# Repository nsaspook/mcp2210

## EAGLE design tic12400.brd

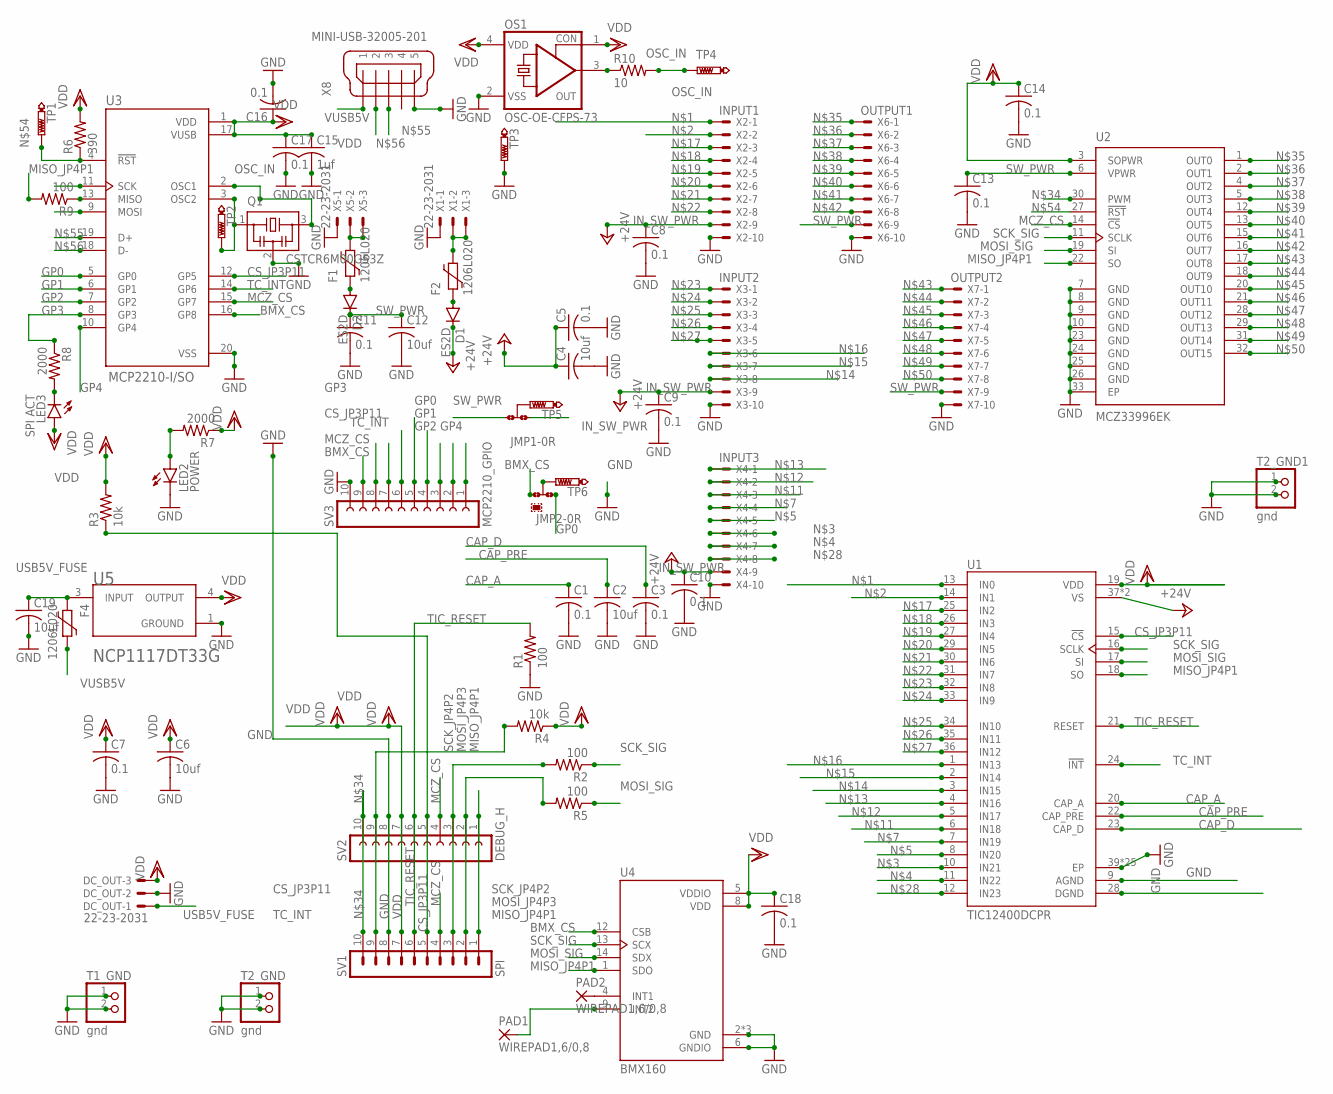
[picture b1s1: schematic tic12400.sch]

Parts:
C1, C3, C5, C7, C8, C9, C10, C11, C13, C14, C16, C17, C18: 0.1; C0805
C2, C4, C6, C12, C19: 10uf; C0805
C15: 1uf; C0805
D1, D2: ES2D; SMB
DC_OUT: 22-23-2031
F1, F2, F4: 1206L020; 1206L
JMP1: +24_CONNECT; A0R-JMP
JMP2: CS8_CS0; A0R-JMP
LED2: POWER; CHIP-LED0805
LED3: SPI ACT; CHIP-LED0805
OS1: OSC-OE-CFPS-73; 7.2X5.2-4-PAD
PAD1, PAD2: WIREPAD1,6/0,8; 1,6/0,8
Q1: CSTCR6M00G53Z; CSTCR6M
R1, R2, R5, R9: 100; R0805
R3, R4: 10k; R0805
R6: 390; R0805
R7, R8: 2000; R0805
R10: 10; R0805
SV1: SPI; MA10-1
SV2: DEBUG_H; FE10
SV3: MCP2210_GPIO; FE10
T1_GND, T2_GND, T2_GND1: gnd; 1X02
TP1, TP2, TP3, TP4, TP5, TP6: PTR1B1,27; B1,27
U1: TIC12400DCPR; SOP50P640X120-38N
U2: MCZ33996EK; SOP65P1030X265-33N
U3: MCP2210-I/SO; SOP65P780X200-20N
U4: BMX160; PQFN50P250X300X100-14N
U5: ON_SEMICONDUCTOR_NCP1117DT33GON_SEMICONDUCTOR_NCP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; ON_SEMICONDUCTOR_NCP1117DT33G_0
X1, X5: 22-23-2031
X2: INPUT1; KK-156-10
X3: INPUT2; KK-156-10
X4: INPUT3; KK-156-10
X6: OUTPUT1; KK-156-10
X7: OUTPUT2; KK-156-10
X8: MINI-USB-32005-201; 32005-201

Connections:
BMX_CS: JMP2.1, SV3.9, U3.16 (GP8), U4.12 (CSB)
CAP_A: C1.1, U1.20 (CAP_A)
CAP_D: C3.1, U1.23 (CAP_D)
CAP_PRE: C2.1, U1.22 (CAP_PRE)
CS_JP3P11: R3.1, SV1.5, SV2.5, SV3.6, U1.15 (!CS), U3.12 (GP5)
GND: C1.2, C2.2, C3.2, C4.2, C5.2, C6.2, C7.2, C8.2, C9.2, C10.2, C11.2, C12.2, C13.2, C14.2, C15.2, C16.2, C17.2, C18.2, C19.2, DC_OUT.2, LED2.C, OS1.2 (VSS), Q1.2, R1.1, SV1.8, SV2.8, SV3.10, T1_GND.1, T1_GND.2, T2_GND.1, T2_GND.2, T2_GND1.1, T2_GND1.2, TP3.TP, U1.9 (AGND), U1.28 (DGND), U1.39 (EP), U1.40 (EP), U1.41 (EP), U1.42 (EP), U1.43 (EP), U1.44 (EP), U1.45 (EP), U1.46 (EP), U1.47 (EP), U1.48 (EP), U1.49 (EP), U1.50 (EP), U1.51 (EP), U1.52 (EP), U1.53 (EP), U1.54 (EP), U1.55 (EP), U1.56 (EP), U1.57 (EP), U1.58 (EP), U1.59 (EP), U1.60 (EP), U1.61 (EP), U1.62 (EP), U1.63 (EP), U2.7 (GND), U2.8 (GND), U2.9 (GND), U2.10 (GND), U2.23 (GND), U2.24 (GND), U2.25 (GND), U2.26 (GND), U2.33 (EP), U3.20 (VSS), U4.2 (GND), U4.3 (GND), U4.6 (GNDIO), U4.7 (GND), U5.1 (GROUND), X1.1, X2.10, X3.10, X4.10, X5.1, X6.10, X7.10, X8.5
GP0: JMP2.3, SV3.1, U3.5 (GP0)
GP1: SV3.2, U3.6 (GP1)
GP2: SV3.3, U3.7 (GP2)
GP3: R8.1, SV3.4, U3.8 (GP3)
GP4: SV3.5, U3.10 (GP4)
IN_SW_PWR: C4.1, C5.1, C8.1, C9.1, C10.1, D1.C, JMP1.3, U1.37 (VS), U1.38 (VS), X2.9, X3.9, X4.9
MCZ_CS: SV1.4, SV2.4, SV3.8, U2.14 (!CS), U3.15 (GP7)
MISO_JP4P1: R9.2, SV1.1, SV2.1, U1.18 (SO), U2.22 (SO), U4.1 (SDO)
MOSI_JP4P3: R5.2, SV1.2, SV2.2
MOSI_SIG: R5.1, U1.17 (SI), U2.19 (SI), U3.9 (MOSI), U4.14 (SDX)
unnamed: U1.13 (IN0), X2.1
unnamed: U1.14 (IN1), X2.2
unnamed: U1.10 (IN21), X4.6
unnamed: U1.11 (IN22), X4.7
unnamed: U1.8 (IN20), X4.5
unnamed: JMP2.2, TP6.TP
unnamed: U1.7 (IN19), X4.4
unnamed: U1.6 (IN18), X4.3
unnamed: U1.5 (IN17), X4.2
unnamed: U1.4 (IN16), X4.1
unnamed: U1.3 (IN15), X3.8
unnamed: U1.2 (IN14), X3.7
unnamed: U1.1 (IN13), X3.6
unnamed: U1.25 (IN2), X2.3
unnamed: U1.26 (IN3), X2.4
unnamed: U1.27 (IN4), X2.5
unnamed: U1.29 (IN5), X2.6
unnamed: U1.30 (IN6), X2.7
unnamed: U1.31 (IN7), X2.8
unnamed: U1.32 (IN8), X3.1
unnamed: U1.33 (IN9), X3.2
unnamed: U1.34 (IN10), X3.3
unnamed: U1.35 (IN11), X3.4
unnamed: U1.36 (IN12), X3.5
unnamed: U1.12 (IN23), X4.8
unnamed: F2.1, X1.2, X1.3
unnamed: D2.A, F1.2
unnamed: F1.1, X5.2, X5.3
unnamed: SV1.10, SV2.10, U2.30 (PWM)
unnamed: U2.1 (OUT0), X6.1
unnamed: U2.2 (OUT1), X6.2
unnamed: U2.4 (OUT2), X6.3
unnamed: U2.5 (OUT3), X6.4
unnamed: U2.12 (OUT4), X6.5
unnamed: U2.13 (OUT5), X6.6
unnamed: U2.15 (OUT6), X6.7
unnamed: U2.16 (OUT7), X6.8
unnamed: U2.17 (OUT8), X7.1
unnamed: U2.18 (OUT9), X7.2
unnamed: U2.20 (OUT10), X7.3
unnamed: U2.21 (OUT11), X7.4
unnamed: U2.28 (OUT12), X7.5
unnamed: U2.29 (OUT13), X7.6
unnamed: U2.31 (OUT14), X7.7
unnamed: U2.32 (OUT15), X7.8
unnamed: D1.A, F2.2
unnamed: Q1.1, TP2.TP, U3.3 (OSC2)
unnamed: R6.1, TP1.TP, U2.27 (!RST), U3.4 (!RST)
unnamed 64: U3.19 (D+), X8.3; also elsewhere on the board
unnamed 65: U3.18 (D-), X8.2; also elsewhere on the board
unnamed: LED2.A, R7.2
unnamed: LED3.C, R8.2
unnamed: R9.1, U3.13 (MISO)
unnamed: OS1.3 (OUT), R10.1
unnamed: JMP1.2, TP5.TP
unnamed 71: PAD2.1, U4.4 (INT1); also elsewhere on the board
unnamed 72: PAD1.1, U4.9 (INT2); also elsewhere on the board
OSC_IN: Q1.3, R10.2, TP4.TP, U3.2 (OSC1)
SCK_JP4P2: R2.2, SV1.3, SV2.3
SCK_SIG: R2.1, U1.16 (SCLK), U2.11 (SCLK), U3.11 (SCK), U4.13 (SCX)
SW_PWR: C11.1, C12.1, C13.1, D2.C, JMP1.1, U2.6 (VPWR), X6.9, X7.9
TC_INT: R4.2, SV1.9, SV2.9, SV3.7, U1.24 (!INT), U3.14 (GP6)
TIC_RESET: R1.2, SV1.6, SV2.6, U1.21 (RESET)
USB5V_FUSE: C19.1, DC_OUT.1, F4.2, U5.3 (INPUT)
VDD: C6.1, C7.1, C14.1, C15.1, C16.1, C17.1, C18.1, DC_OUT.3, LED3.A, OS1.1 (CON), OS1.4 (VDD), R3.2, R4.1, R6.2, R7.1, SV1.7, SV2.7, U1.19 (VDD), U2.3 (SOPWR), U3.1 (VDD), U3.17 (VUSB), U4.5 (VDDIO), U4.8 (VDD), U5.4 (OUTPUT)
VUSB5V: F4.1, X8.1

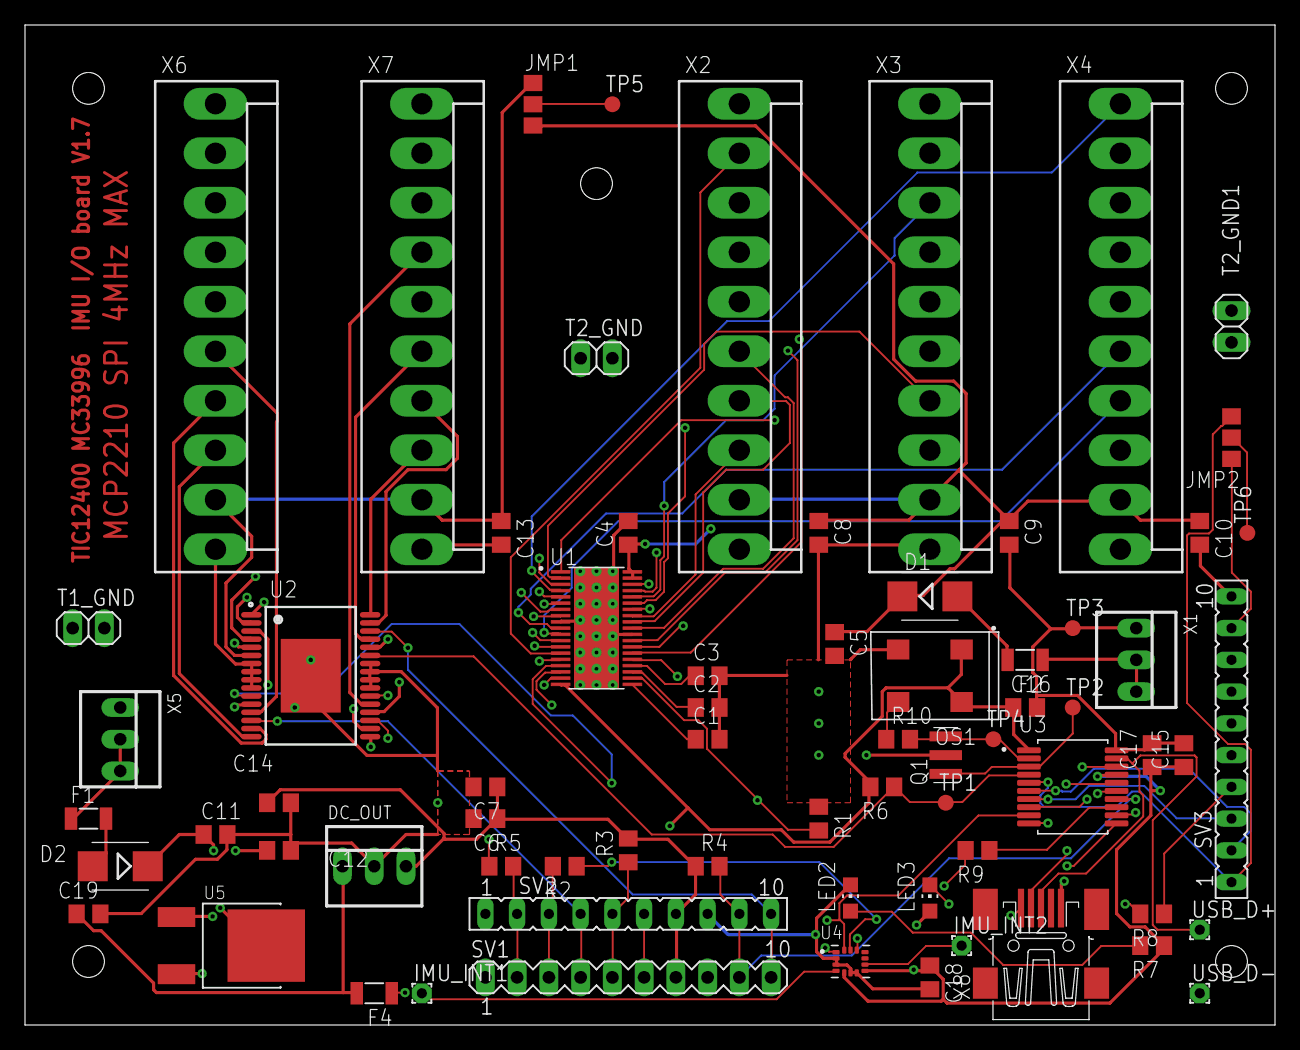
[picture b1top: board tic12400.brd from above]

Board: 4 copper layers, 100.0 x 80.0 mm, 70 parts (0 on the bottom side), 82 nets.

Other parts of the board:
IMU_INT1: int1; 1,6/0,8
IMU_INT2: int2; 1,6/0,8
USB_D+: d+; 1,6/0,8
USB_D-: d-; 1,6/0,8

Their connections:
unnamed 64: USB_D+.1; also elsewhere on the board
unnamed 65: USB_D-.1; also elsewhere on the board
unnamed 71: IMU_INT1.1; also elsewhere on the board
unnamed 72: IMU_INT2.1; also elsewhere on the board

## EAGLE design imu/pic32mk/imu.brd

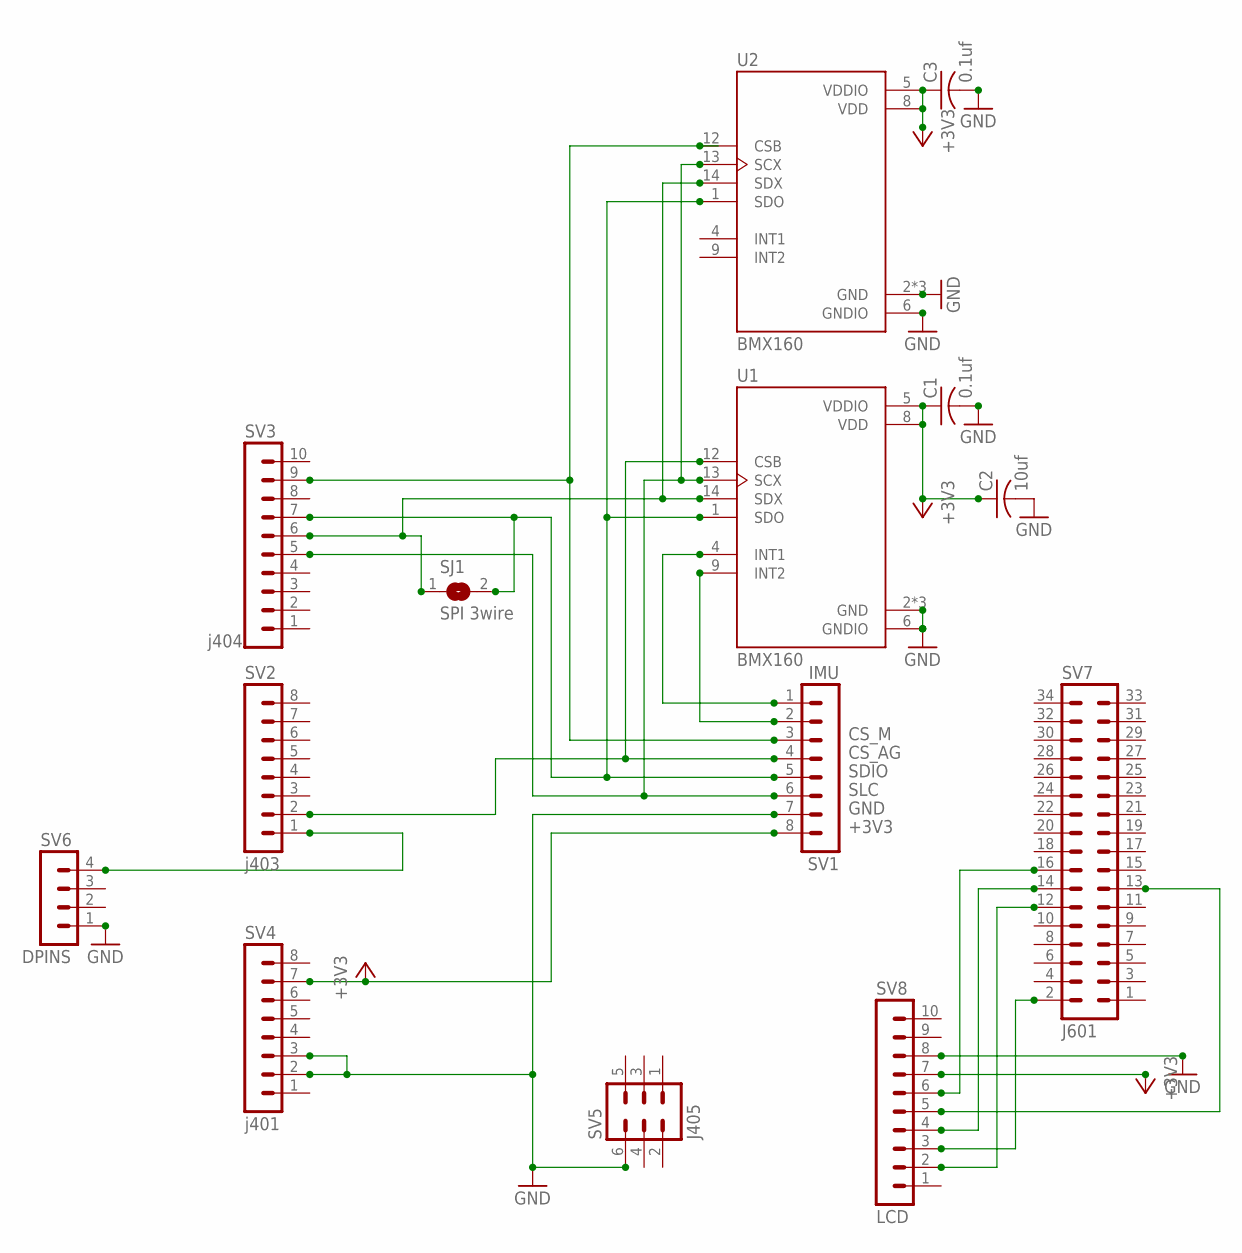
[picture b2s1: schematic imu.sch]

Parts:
C1, C3: 0.1uf; C0805
C2: 10uf; C0805
SJ1: SPI 3wire; SJ
SV1: IMU; MA08-1
SV2: j403; MA08-1
SV3: j404; MA10-1
SV4: j401; MA08-1
SV5: J405; MA03-2
SV6: DPINS; MA04-1
SV7: J601; MA17-2W
SV8: LCD; MA10-1
U1, U2: BMX160; PQFN50P250X300X100-14N

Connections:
+3V3: C1.1, C2.1, C3.1, SV1.8, SV4.7, SV8.7, U1.5 (VDDIO), U1.8 (VDD), U2.5 (VDDIO), U2.8 (VDD)
CS_AG: SV1.4, SV2.2, U1.12 (CSB)
CS_M: SV1.3, SV3.9, U2.12 (CSB)
GND: C1.2, C2.2, C3.2, SV1.7, SV4.2, SV4.3, SV5.6, SV6.1, SV8.8, U1.2 (GND), U1.3 (GND), U1.6 (GNDIO), U1.7 (GND), U2.2 (GND), U2.3 (GND), U2.6 (GNDIO), U2.7 (GND)
unnamed: SV7.2, SV8.3
unnamed: SV2.1, SV6.4
unnamed: SV7.12, SV8.2
unnamed: SV7.13, SV8.5
unnamed: SV7.14, SV8.4
unnamed: SV7.16, SV8.6
unnamed: SJ1.1, SV3.6, U1.14 (SDX), U2.14 (SDX)
unnamed: SV1.2, U1.9 (INT2)
unnamed: SV1.1, U1.4 (INT1)
SDIO: SJ1.2, SV1.5, SV3.7, U1.1 (SDO), U2.1 (SDO)
SLC: SV1.6, SV3.5, U1.13 (SCX), U2.13 (SCX)

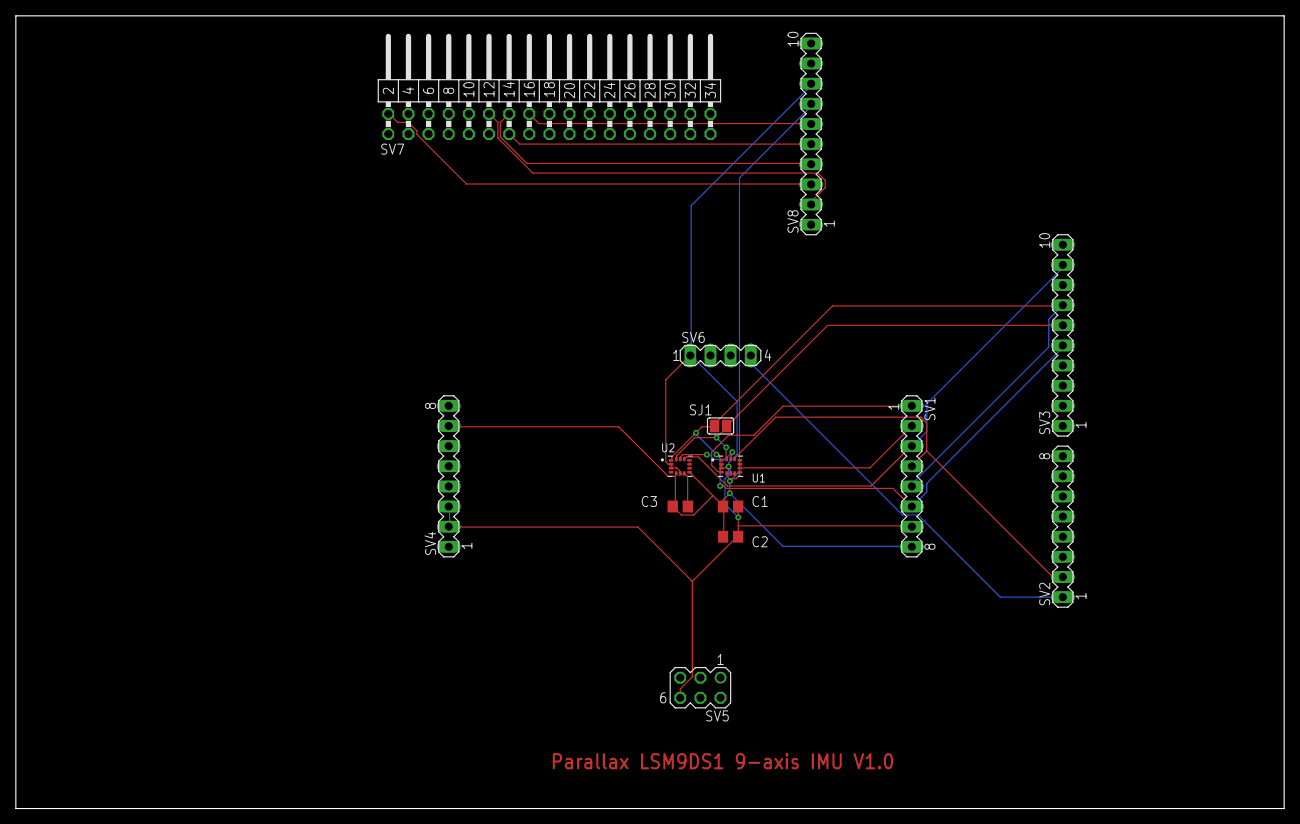
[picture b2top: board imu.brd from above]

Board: 2 copper layers, 160.0 x 100.0 mm, 14 parts (0 on the bottom side), 15 nets.

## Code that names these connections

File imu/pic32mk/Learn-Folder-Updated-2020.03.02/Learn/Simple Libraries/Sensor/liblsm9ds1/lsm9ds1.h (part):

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 *
 * @param pinSCL I/O Pin connected to the module's SCL pin.  
 *
 * @param pinSDIO I/O Pin connected to the module's SDIO pin.  
 *
 * @param pinAG I/O Pin connected to the module's CS_AG pin.  
 *
 * @param pinM I/O Pin connected to the module's CS_M pin.  
 *
 * @returns 0x683D if both the Accel/Gyro and Mag start up successfully,  
 * or 0 of neither sensor starts.
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
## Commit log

2021-12-14 update to BMX160 code

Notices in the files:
imu/pic32mk/Learn-Folder-Updated-2020.03.02/Learn/Simple Libraries/Sensor/liblsm9ds1/lsm9ds1.h:
Copyright (C) Parallax, Inc. 2016. All Rights MIT Licensed.
TERMS OF USE: MIT License
